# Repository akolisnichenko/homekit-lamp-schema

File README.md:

# homekit-lamp-schema
PCB for homekit lamp

Here is KiCad schema for PCB with support homekit lamp

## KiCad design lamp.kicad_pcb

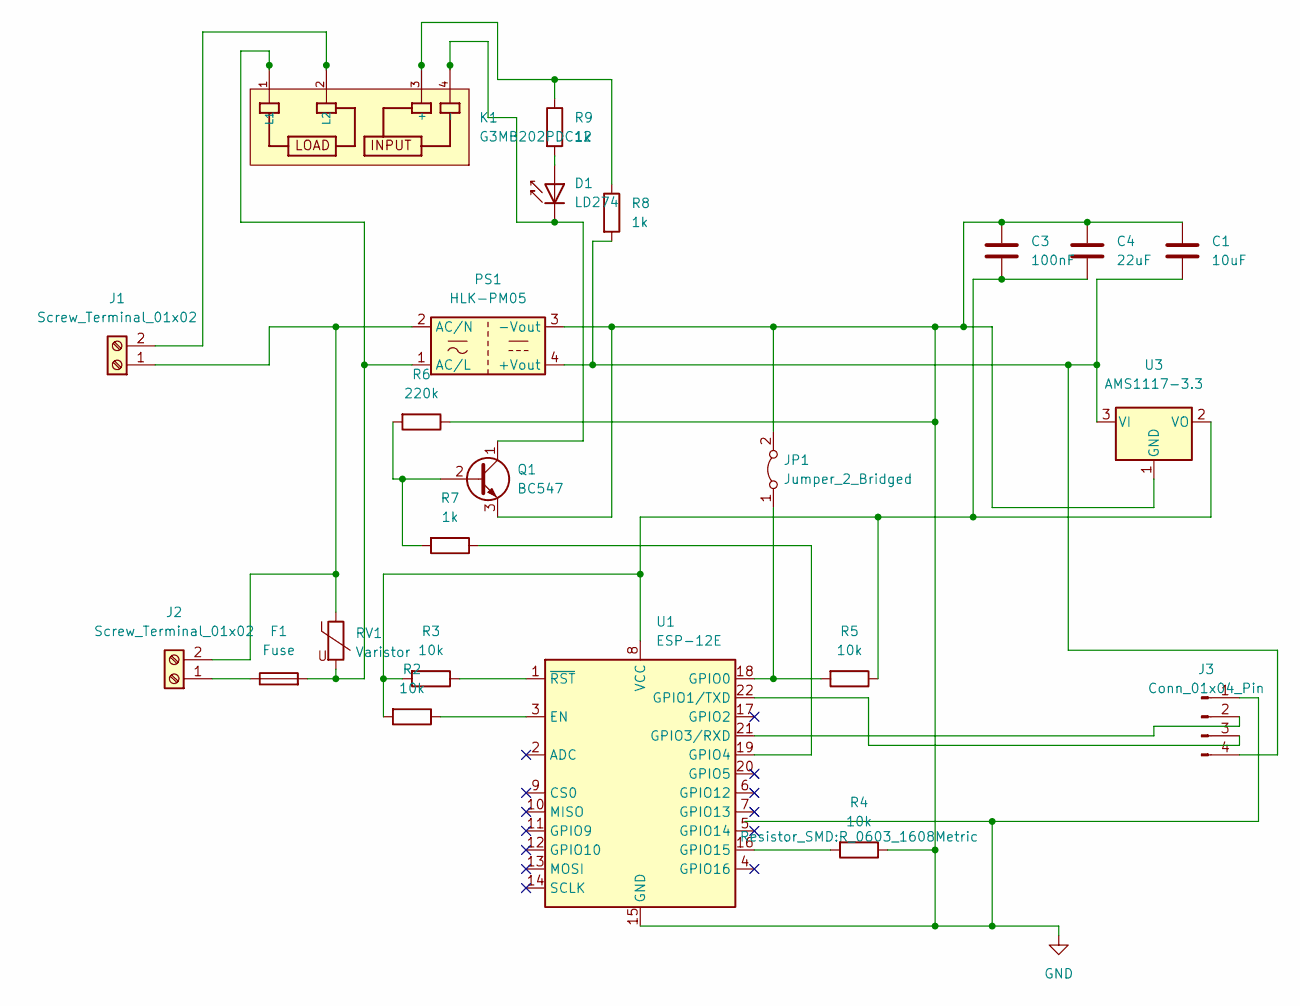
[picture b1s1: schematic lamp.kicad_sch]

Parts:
C1: 10uF; CP_Radial_D5.0mm_P2.50mm
C3: 100nF; CP_Radial_D5.0mm_P2.50mm
C4: 22uF; CP_Radial_D5.0mm_P2.50mm
D1: LD274; LED_D5.0mm_IRGrey
F1: Fuse; Fuse_Bourns_MF-RG400
J1, J2: Screw_Terminal_01x02; TerminalBlock_Altech_AK300-2_P5.00mm
J3: Conn_01x04_Pin; PinHeader_1x04_P2.54mm_Vertical
JP1: Jumper_2_Bridged; TestPoint_2Pads_Pitch2.54mm_Drill0.8mm
K1: G3MB202PDC12; RELAY_G3MB202PDC12; PARTREV N/A
PS1: HLK-PM05; Converter_ACDC_HiLink_HLK-PMxx
Q1: BC547; TO-92_Inline
R2, R3, R4, R5: 10k; R_0603_1608Metric
R6: 220k; R_0603_1608Metric
R7, R8, R9: 1k; R_0603_1608Metric
RV1: Varistor; RV_Disc_D9mm_W4.4mm_P5mm
U1: ESP-12E
U3: AMS1117-3.3; SOT-223-3_TabPin2

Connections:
GND: C1.1, C3.1, C4.1, J3.1, JP1.2 (B), PS1.3 (-Vout), Q1.3 (E), R4.1, R6.1, U1.15 (GND), U3.1 (GND)
unnamed: D1.2 (A), R9.2
unnamed: D1.1 (K), K1.4 (-), Q1.1 (C)
unnamed: J1.1, J2.2, PS1.2 (AC/N), RV1.1
unnamed: J1.2, K1.2 (L2)
unnamed: F1.1, J2.1
unnamed: J3.2, U1.21 (GPIO3/RXD)
unnamed: J3.3, U1.22 (GPIO1/TXD)
unnamed: C1.2, J3.4, PS1.4 (+Vout), R8.2, U3.3 (VI)
unnamed: JP1.1 (A), R5.2, U1.18 (GPIO0)
unnamed: K1.3 (+), R8.1, R9.1
unnamed: F1.2, K1.1 (L1), PS1.1 (AC/L), RV1.2
unnamed: Q1.2 (B), R6.2, R7.2
unnamed: R2.1, U1.3 (EN)
unnamed: R7.1, U1.19 (GPIO4)
unnamed: R4.2, U1.16 (GPIO15)
unnamed: C3.2, C4.2, R2.2, R3.2, R5.1, U1.8 (VCC), U3.2 (VO)
unnamed: R3.1, U1.1 (~RST)

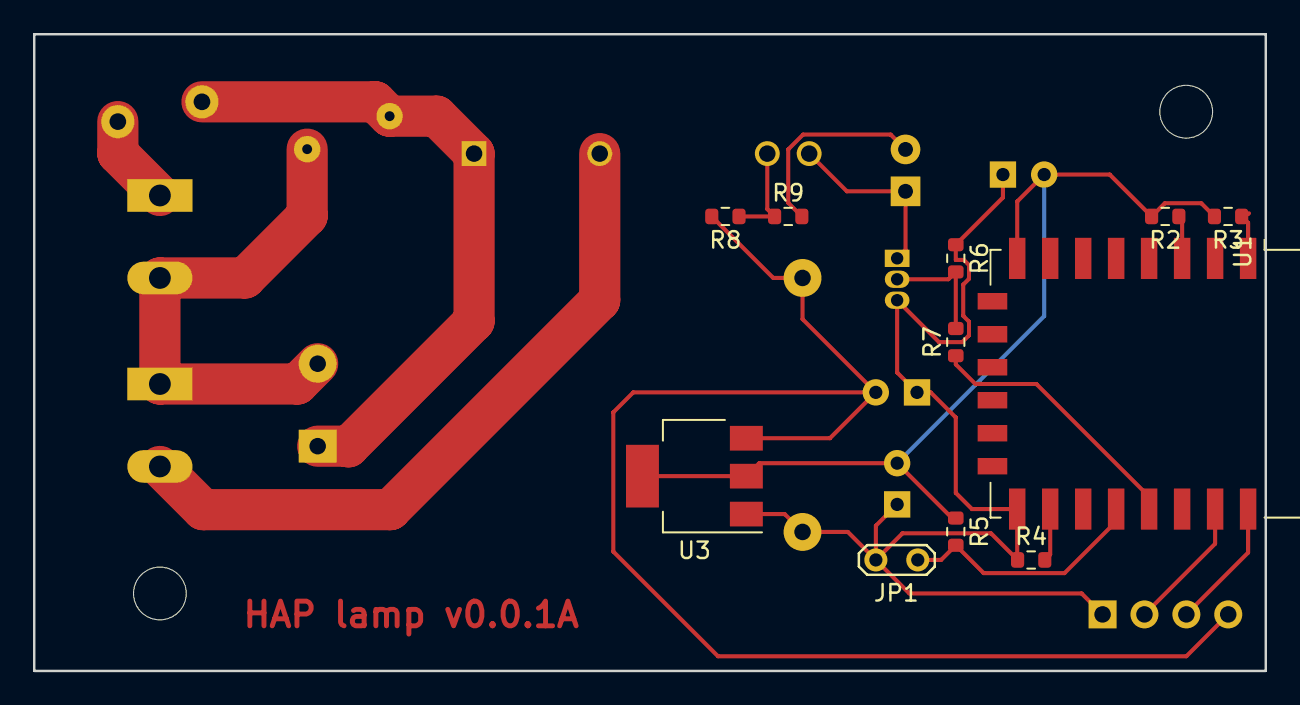
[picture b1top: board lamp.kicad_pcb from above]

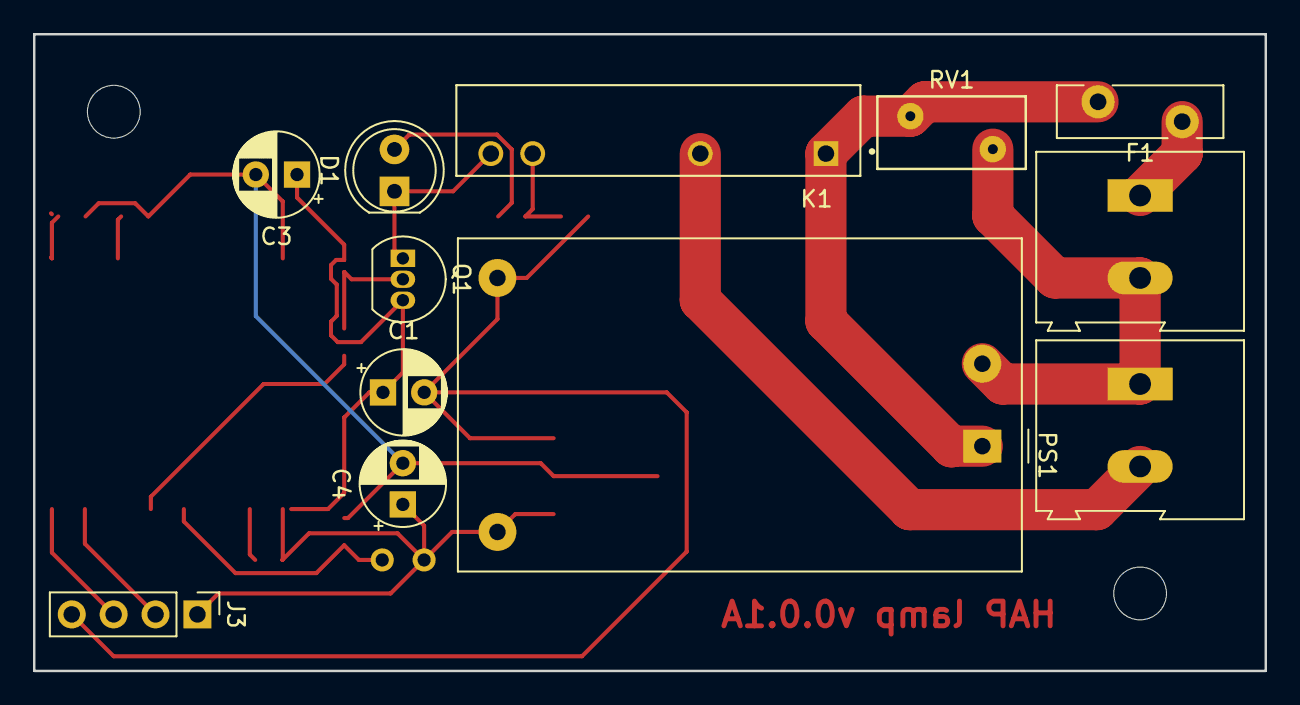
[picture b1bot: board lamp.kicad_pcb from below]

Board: 2 copper layers, 74.7 x 38.6 mm, 23 parts (12 on the bottom side), 18 nets.

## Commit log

2023-03-25 some chnges
    some changes
2023-03-25 schema changes
2023-03-25 updated after telegram comments
2023-05-31 0.1 revision
    broken tracing
    fixed capacitor footprint
2023-09-03 updated v0.0.1A
    update
2023-09-03 minor fixes
2023-09-03 fix jumper side
